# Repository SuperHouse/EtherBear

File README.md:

SuperHouse EtherBear
=====================

The EtherBear is an Arduino compatible development board for the
ATmega1284P microcontroller, with a Wiznet W6100 Ethernet interface and
Power-over-Ethernet support.

The W6100 provides both IPv4 and IPv6 support.

Features:

 * LEDs visible on the edge
 * USB-C Connector
 * I2C MAC address ROM
 * Overlay guide where you need it (both top and bottom)
 * D13 pin works for everything
 * RX pin biased
 * Mounting holes

More information is available at:

  https://www.superhouse.tv/etherbear

Hardware
--------
The "Hardware" directory contains the PCB design as an EAGLE project.
EAGLE PCB design software is available from Autodesk free for
non-commercial use.

Credits
-------
 * Jonathan Oxer <jon@oxer.com.au>

The EtherBear is based on the EtherUNO, which in turn is based on the
EtherTen, which was designed by Jonathan Oxer and Marc Alexander.

License
-------
Copyright 2020 SuperHouse Automation Pty Ltd  www.superhouse.tv  

The hardware portion of this project is licensed under the TAPR Open
Hardware License (www.tapr.org/OHL). The "license" folder within this
repository contains a copy of this license in plain text format.

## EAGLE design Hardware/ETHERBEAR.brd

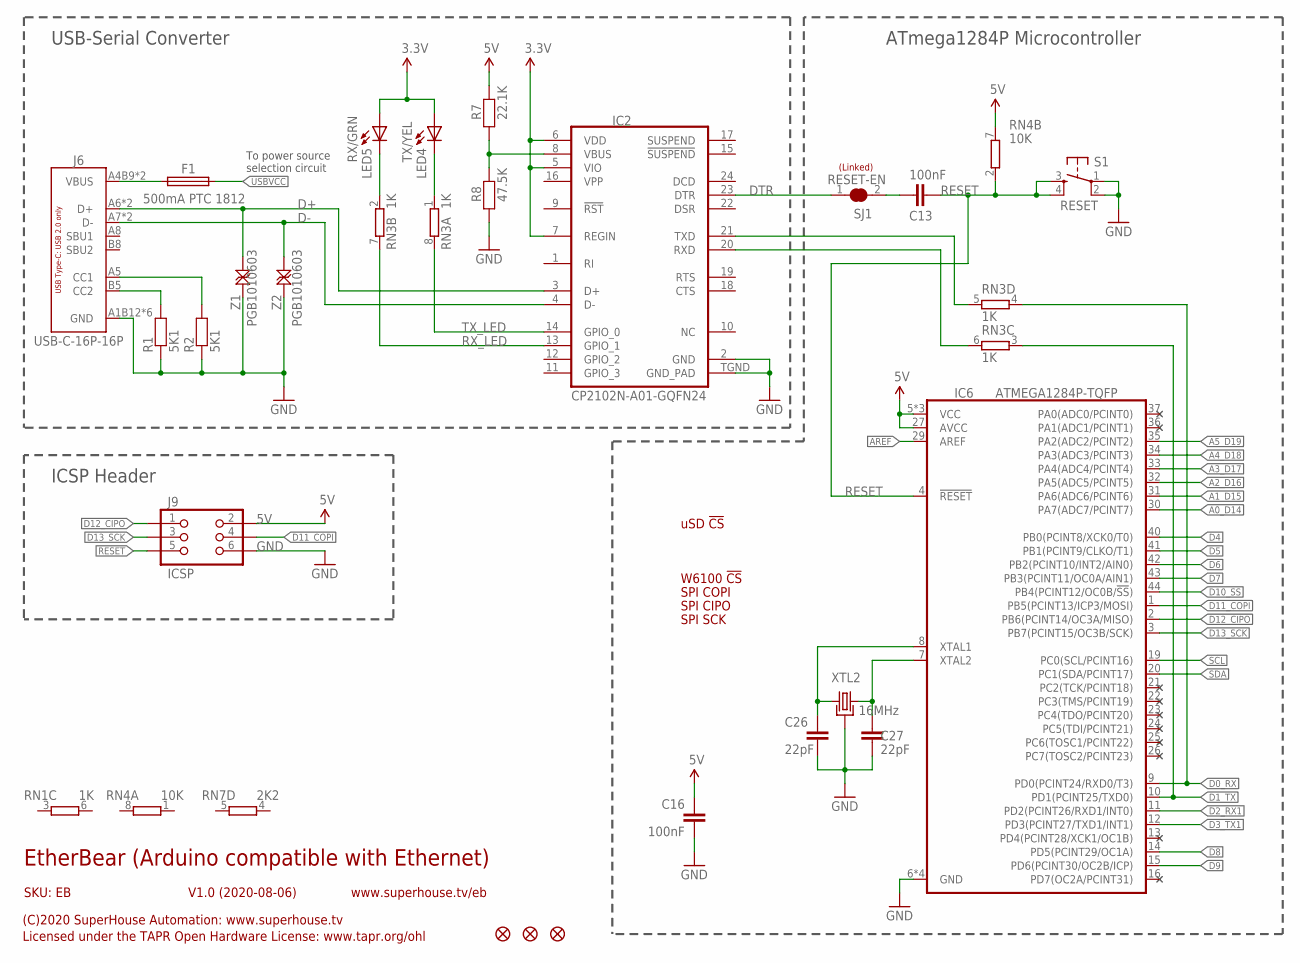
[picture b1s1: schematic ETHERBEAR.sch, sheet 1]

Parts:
C13, C16: 100nF; C0603
C26, C27: 22pF; C0603
F1: 500mA PTC 1812; 1812
FID1, FID2, FID3: FIDUCIAL1X2.5; FIDUCIAL-1X2.5
IC2: CP2102N-A01-GQFN24; QFN-24
IC6: ATMEGA1284P-TQFP; TQFP44
J6: USB-C-16P-16P; USB-C-16P
J9: ICSP; 2X03-ICSP
LED4: TX/YEL; LED-0603
LED5: RX/GRN; LED-0603
R1, R2: 5K1; R0603
R7: 22.1K; R0603
R8: 47.5K; R0603
RN1, RN3: 1K; CAY16
RN4: 10K; CAY16
RN7: 2K2; CAY16
S1: RESET; TACTILE_SMT-6MM
SJ1: RESET-EN; SJC
XTL2: 16MHz; CRYSTAL-SMD-3X2
Z1, Z2: PGB1010603; TVS0603

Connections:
3.3V: IC2.5 (VIO), IC2.6 (VDD), IC2.7 (REGIN), LED4.A, LED5.A; also elsewhere on the board
5V: C16.1, IC6.5 (VCC), IC6.17 (VCC), IC6.27 (AVCC), IC6.28 (VCC), J9.2, R7.2, RN4.7 (2); also elsewhere on the board
A0_D14: IC6.30 (PA7(ADC7/PCINT7)); also elsewhere on the board
A1_D15: IC6.31 (PA6(ADC6/PCINT6)); also elsewhere on the board
A2_D16: IC6.32 (PA5(ADC5/PCINT5)); also elsewhere on the board
A3_D17: IC6.33 (PA4(ADC4/PCINT4)); also elsewhere on the board
A4_D18: IC6.34 (PA3(ADC3/PCINT3)); also elsewhere on the board
A5_D19: IC6.35 (PA2(ADC2/PCINT2)); also elsewhere on the board
AREF: IC6.29 (AREF); also elsewhere on the board
D0_RX: IC6.9 (PD0(PCINT24/RXD0/T3)), RN3.4 (1); also elsewhere on the board
D1_TX: IC6.10 (PD1(PCINT25/TXD0)), RN3.3 (1); also elsewhere on the board
D2_RX1: IC6.11 (PD2(PCINT26/RXD1/INT0)); also elsewhere on the board
D3_TX1: IC6.12 (PD3(PCINT27/TXD1/INT1)); also elsewhere on the board
D4: IC6.40 (PB0(PCINT8/XCK0/T0)); also elsewhere on the board
D5: IC6.41 (PB1(PCINT9/CLKO/T1)); also elsewhere on the board
D6: IC6.42 (PB2(PCINT10/INT2/AIN0)); also elsewhere on the board
D7: IC6.43 (PB3(PCINT11/OC0A/AIN1)); also elsewhere on the board
D8: IC6.14 (PD5(PCINT29/OC1A)); also elsewhere on the board
D9: IC6.15 (PD6(PCINT30/OC2B/ICP)); also elsewhere on the board
D10_SS: IC6.44 (PB4(PCINT12/OC0B/!SS!))
D11_COPI: IC6.1 (PB5(PCINT13/ICP3/MOSI)), J9.4; also elsewhere on the board
D12_CIPO: IC6.2 (PB6(PCINT14/OC3A/MISO)), J9.1; also elsewhere on the board
D13_SCK: IC6.3 (PB7(PCINT15/OC3B/SCK)), J9.3; also elsewhere on the board
D+: IC2.3 (D+), J6.A6 (D+), J6.B6 (D+), Z1.1
D-: IC2.4 (D-), J6.A7 (D-), J6.B7 (D-), Z2.1
DTR: IC2.23 (DTR), SJ1.1
GND: C16.2, C26.1, C27.1, IC2.2 (GND), IC2.TGND (GND_PAD), IC6.6 (GND), IC6.18 (GND), IC6.38 (GND), IC6.39 (GND), J6.A1B12 (GND), J6.A12B1 (GND), J6.FIX1 (GND), J6.FIX2 (GND), J6.FIX3 (GND), J6.FIX4 (GND), J9.6, R1.1, R2.1, R8.1, S1.1, S1.2, XTL2.2 (GND), XTL2.4 (GND), Z1.2, Z2.2; also elsewhere on the board
unnamed: C26.2, IC6.8 (XTAL1), XTL2.1
unnamed: C13.1, SJ1.2
unnamed: C27.2, IC6.7 (XTAL2), XTL2.3 (2)
unnamed: J6.B5 (CC2), R1.2
unnamed: LED5.C, RN3.2 (1)
unnamed: LED4.C, RN3.1
unnamed: J6.A5 (CC1), R2.2
unnamed: IC2.8 (VBUS), R7.1, R8.2
unnamed: F1.1, J6.A4B9 (VBUS), J6.A9B4 (VBUS)
RESET: C13.2, IC6.4 (!RESET), J9.5, RN4.2 (1), S1.3, S1.4; also elsewhere on the board
RX_LED: IC2.13 (GPIO_1), RN3.7 (2)
SCL: IC6.19 (PC0(SCL/PCINT16)); also elsewhere on the board
SDA: IC6.20 (PC1(SDA/PCINT17)); also elsewhere on the board
TX_LED: IC2.14 (GPIO_0), RN3.8 (2)
USBRXD: IC2.21 (TXD), RN3.5 (2)
USBTXD: IC2.20 (RXD), RN3.6 (2)
USBVCC: F1.2; also elsewhere on the board

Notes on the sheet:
(Linked)
EtherBear (Arduino compatible with Ethernet)
SKU: EB
(C)2020 SuperHouse Automation: www.superhouse.tv
Licensed under the TAPR Open Hardware License: www.tapr.org/ohl
www.superhouse.tv/eb
V1.0 (2020-08-06)
USB-Serial Converter
ATmega1284P Microcontroller
ICSP Header
To power source selection circuit
uSD !CS
W6100 !CS
SPI COPI
SPI CIPO
SPI SCK

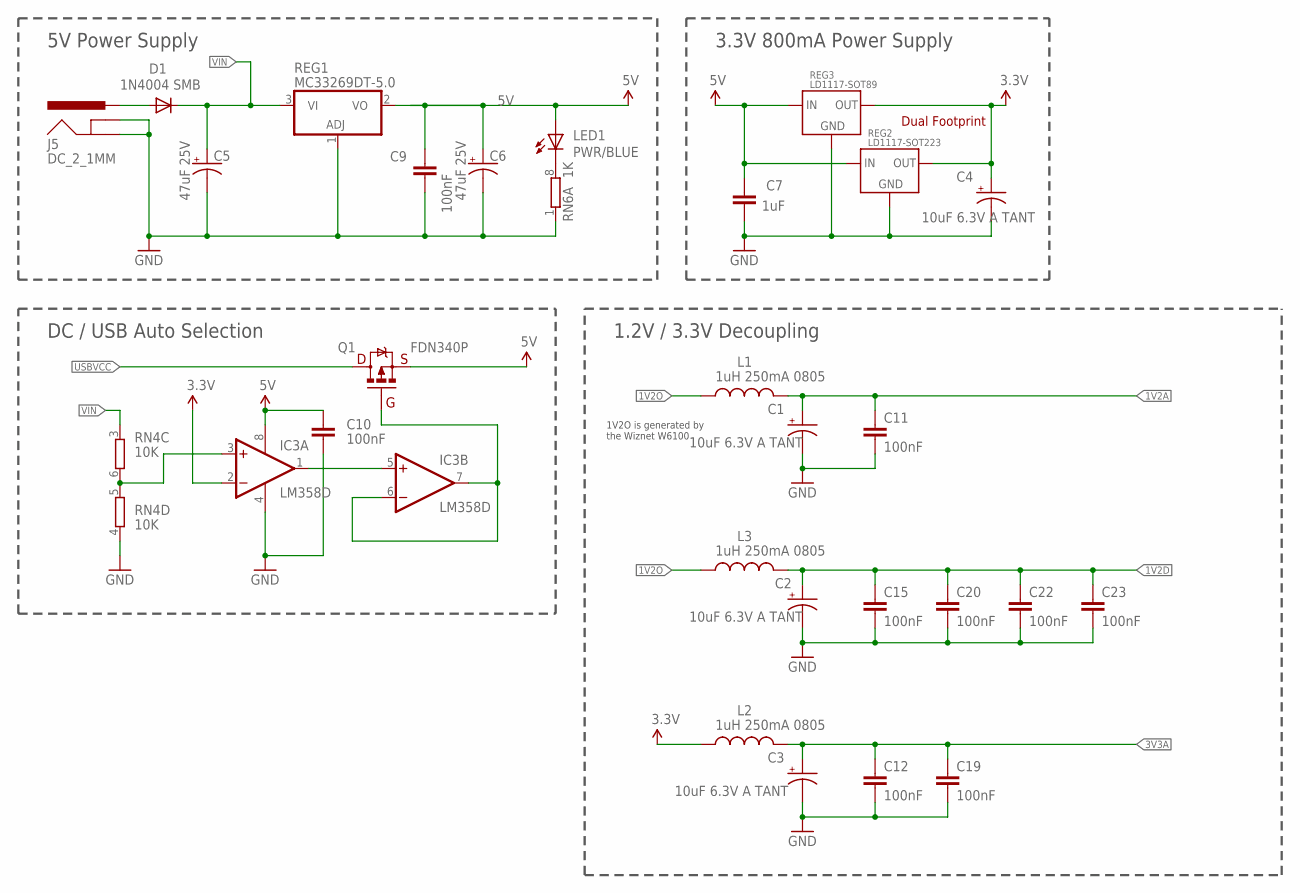
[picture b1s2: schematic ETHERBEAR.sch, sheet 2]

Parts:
C1, C2, C3, C4: 10uF 6.3V A TANT; EIA3216
C5, C6: 47uF 25V; PANASONIC_D
C7: 1uF; C0603
C9, C10, C11, C12, C15, C19, C20, C22, C23: 100nF; C0603
D1: 1N4004 SMB; SMA-DIODE
IC3: LM358D; SO08
J5: DC_2_1MM; POWER_JACK_SLOTS
L1, L2, L3: 1uH 250mA 0805; 0805-LARGE
LED1: PWR/BLUE; LED-0603
Q1: FDN340P; SOT23
REG1: MC33269DT-5.0; DPACK
REG2: LD1117-SOT223; SOT-223
REG3: LD1117-SOT89; SOT89
RN4: 10K; CAY16
RN6: 1K; CAY16

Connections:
1V2A: C1.A (+), C11.1, L1.2; also elsewhere on the board
1V2D: C2.A (+), C15.1, C20.1, C22.1, C23.1, L3.2; also elsewhere on the board
1V2O: L1.1, L3.1; also elsewhere on the board
3.3V: C4.A (+), IC3.2 (-IN), L2.1, REG2.2 (OUT), REG2.4 (OUT), REG3.2 (OUT), REG3.4 (OUT); also elsewhere on the board
3V3A: C3.A (+), C12.1, C19.1, L2.2; also elsewhere on the board
5V: C6.+, C7.1, C9.1, C10.1, IC3.8 (V+), LED1.A, Q1.2 (S), REG1.2 (VO), REG2.3 (IN), REG3.3 (IN); also elsewhere on the board
GND: C1.C (-), C2.C (-), C3.C (-), C4.C (-), C5.-, C6.-, C7.2, C9.2, C10.2, C11.2, C12.2, C15.2, C19.2, C20.2, C22.2, C23.2, IC3.4 (V-), J5.GND, J5.GNDBREAK, REG1.1 (ADJ), REG2.1 (GND), REG3.1 (GND), RN4.4 (1), RN6.1; also elsewhere on the board
unnamed: IC3.3 (+IN), RN4.5 (2), RN4.6 (2)
unnamed: LED1.C, RN6.8 (2)
unnamed: IC3.6 (-IN), IC3.7 (OUT), Q1.1 (G)
unnamed: IC3.1 (OUT), IC3.5 (+IN)
unnamed: D1.A, J5.PWR
USBVCC: Q1.3 (D); also elsewhere on the board
VIN: C5.+, D1.C, REG1.3 (VI), RN4.3 (1); also elsewhere on the board

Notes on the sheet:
Dual Footprint
1V2O is generated by the Wiznet W6100
1.2V / 3.3V Decoupling
3.3V 800mA Power Supply
5V Power Supply
DC / USB Auto Selection

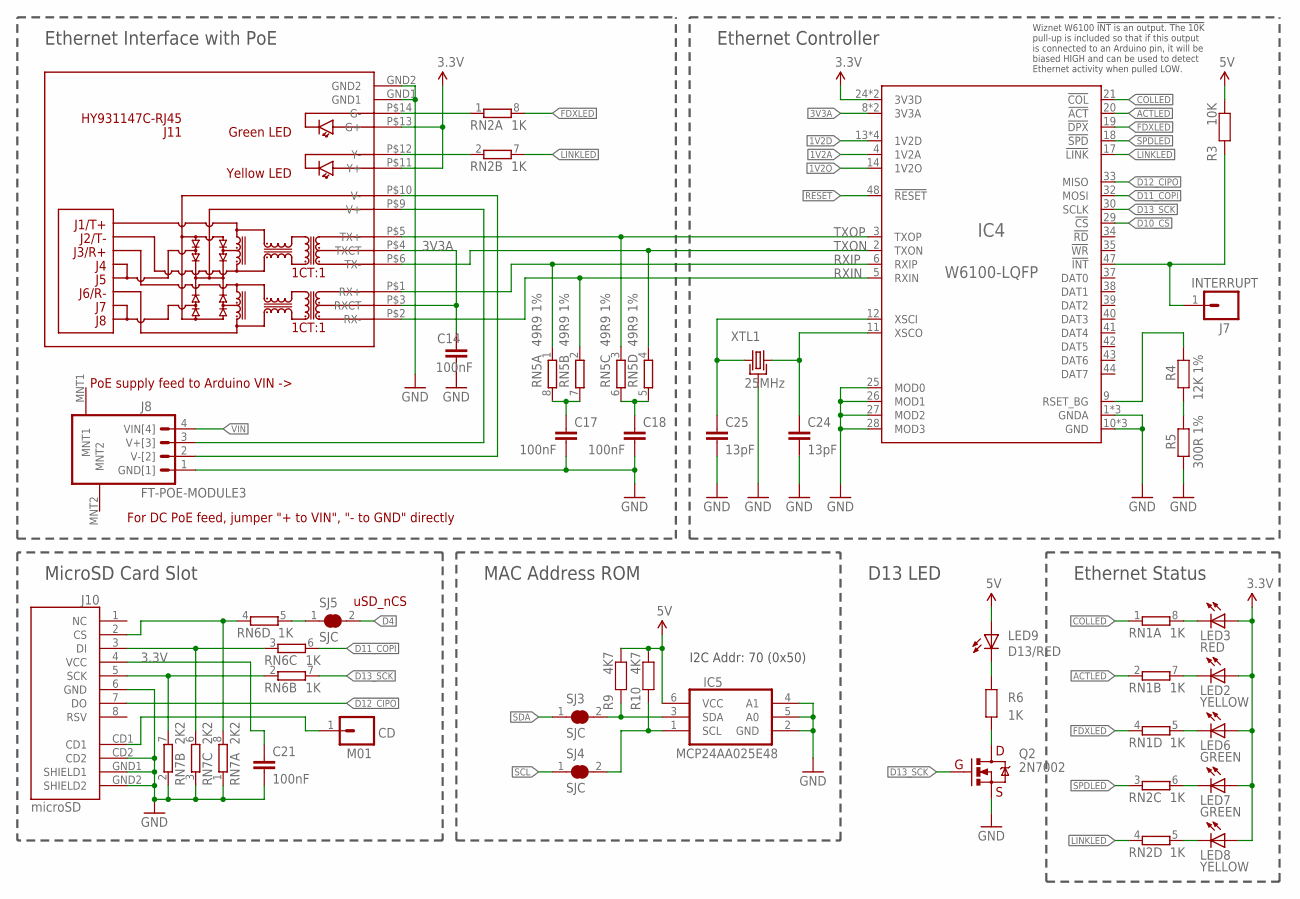
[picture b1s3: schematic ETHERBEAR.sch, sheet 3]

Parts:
C14, C17, C18, C21: 100nF; C0603
C24, C25: 13pF; C0603
CD: M01; 1X01
IC4: W6100-LQFP; LQFP48
IC5: MCP24AA025E48; SOT23-6
J7: INTERRUPT; 1X01
J8: FT-POE-MODULE3; FT-POE-MODULE-NOLABEL
J10: microSD; MICRO-SD-SOCKET-PP
J11: HY931147C-RJ45; HY931147C
LED2, LED8: YELLOW; LED-0603
LED3: RED; LED-0603
LED6, LED7: GREEN; LED-0603
LED9: D13/RED; LED-0603
Q2: 2N7002; SOT23-3
R3: 10K; R0603
R4: 12K 1%; R0603
R5: 300R 1%; R0603
R6: 1K; R0603
R9, R10: 4K7; R0603
RN1, RN2, RN6: 1K; CAY16
RN5: 49R9 1%; CAY16
RN7: 2K2; CAY16
SJ3, SJ4, SJ5: SJC
XTL1: 25MHz; CRYSTAL-SMD-3X2

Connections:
1V2A: IC4.4 (1V2A); also elsewhere on the board
1V2D: IC4.13 (1V2D), IC4.22 (1V2D), IC4.31 (1V2D), IC4.45 (1V2D); also elsewhere on the board
1V2O: IC4.14 (1V2O); also elsewhere on the board
3.3V: C21.1, IC4.24 (3V3D), IC4.36 (3V3D), J10.4 (VCC), J11.P$11 (Y+), J11.P$13 (G+), LED2.A, LED3.A, LED6.A, LED7.A, LED8.A; also elsewhere on the board
3V3A: C14.1, IC4.8 (3V3A), IC4.15 (3V3A), J11.P$3 (RXCT), J11.P$4 (TXCT); also elsewhere on the board
5V: IC5.6 (VCC), LED9.A, R3.1, R9.1, R10.1; also elsewhere on the board
ACTLED: IC4.20 (!ACT), RN1.2 (1)
COLLED: IC4.21 (!COL), RN1.1
D4: SJ5.2; also elsewhere on the board
D10_CS: IC4.29 (!CS); also elsewhere on the board
D11_COPI: IC4.32 (MOSI), RN6.6 (2); also elsewhere on the board
D12_CIPO: IC4.33 (MISO), J10.7 (DO); also elsewhere on the board
D13_SCK: IC4.30 (SCLK), Q2.1 (G), RN6.7 (2); also elsewhere on the board
FDXLED: IC4.19 (!DPX), RN1.4 (1), RN2.8 (2)
GND: C14.2, C17.2, C18.2, C21.2, C24.2, C25.2, IC4.1 (GNDA), IC4.7 (GNDA), IC4.10 (GND), IC4.16 (GNDA), IC4.23 (GND), IC4.25 (MOD0), IC4.26 (MOD1), IC4.27 (MOD2), IC4.28 (MOD3), IC4.46 (GND), IC5.2 (GND), IC5.4 (A1), IC5.5 (A0), J8.1 (GND[1]), J10.6 (GND), J10.CD2, J10.GND1 (SHIELD1), J10.GND2 (SHIELD2), J11.GND1, J11.GND2, Q2.2 (S), R5.2, RN7.1, RN7.2 (1), RN7.3 (1), XTL1.2 (GND), XTL1.4 (GND); also elsewhere on the board
LINKLED: IC4.17 (!LINK), RN2.4 (1), RN2.7 (2)
unnamed: C18.1, RN5.5 (2), RN5.6 (2)
unnamed: LED9.C, R6.2
unnamed: IC5.1 (SCL), R10.2, SJ4.2
unnamed: Q2.3 (D), R6.1
unnamed: LED3.C, RN1.8 (2)
unnamed: IC4.47 (!INT), J7.1, R3.2
unnamed: J10.2 (CS), RN6.4 (1), RN7.8 (2)
unnamed: CD.1, J10.CD1
unnamed: J10.5 (SCK), RN6.2 (1), RN7.7 (2)
unnamed: J10.3 (DI), RN6.3 (1), RN7.6 (2)
unnamed: LED7.C, RN2.6 (2)
unnamed: RN6.5 (2), SJ5.1
unnamed: LED8.C, RN2.5 (2)
unnamed: IC5.3 (SDA), R9.2, SJ3.2
unnamed: C24.1, IC4.11 (XSCO), XTL1.3 (2)
unnamed: C25.1, IC4.12 (XSCI), XTL1.1
unnamed: R4.2, R5.1
unnamed: IC4.9 (RSET_BG), R4.1
unnamed: J11.P$14 (G-), RN2.1
unnamed: J8.3 (V+[3]), J11.P$9 (V+)
unnamed: J8.2 (V-[2]), J11.P$10 (V-)
unnamed: C17.1, RN5.7 (2), RN5.8 (2)
unnamed: LED6.C, RN1.5 (2)
unnamed: LED2.C, RN1.7 (2)
unnamed: J11.P$12 (Y-), RN2.2 (1)
RESET: IC4.48 (!RESET); also elsewhere on the board
RXIN: IC4.5 (RXIN), J11.P$2 (RX-), RN5.2 (1)
RXIP: IC4.6 (RXIP), J11.P$1 (RX+), RN5.1
SCL: SJ4.1; also elsewhere on the board
SDA: SJ3.1; also elsewhere on the board
SPDLED: IC4.18 (!SPD), RN2.3 (1)
TXON: IC4.2 (TXON), J11.P$6 (TX-), RN5.4 (1)
TXOP: IC4.3 (TXOP), J11.P$5 (TX+), RN5.3 (1)
VIN: J8.4 (VIN[4]); also elsewhere on the board

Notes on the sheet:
PoE supply feed to Arduino VIN ->
For DC PoE feed, jumper "+ to VIN", "- to GND" directly
I2C Addr: 70 (0x50)
uSD_nCS
Ethernet Interface with PoE
Ethernet Controller
MAC Address ROM
MicroSD Card Slot
Ethernet Status
Wiznet W6100 !INT is an output. The 10K pull-up is included so that if this output is connected to an Arduino pin, it will be biased HIGH and can be used to detect Ethernet activity when pulled LOW.
D13 LED

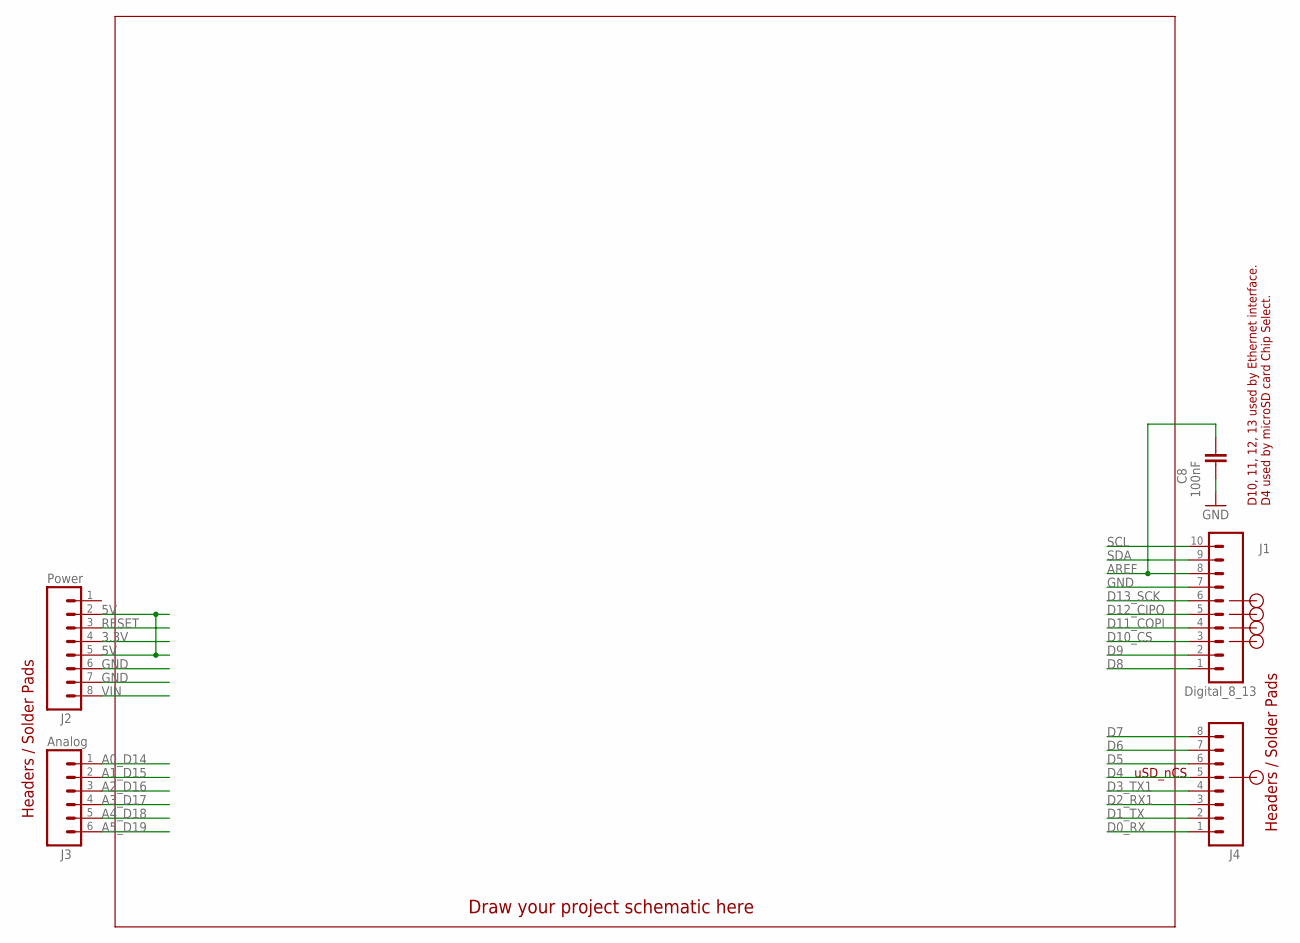
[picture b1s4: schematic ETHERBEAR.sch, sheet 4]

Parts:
C8: 100nF; C0603
J1: Digital_8_13; 1X10-S
J2: Power; 1X08-S
J3: Analog; 1X06-S
J4: Digital_0_7; 1X08-S

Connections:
3.3V: J2.4; also elsewhere on the board
5V: J2.2, J2.5; also elsewhere on the board
A0_D14: J3.1; also elsewhere on the board
A1_D15: J3.2; also elsewhere on the board
A2_D16: J3.3; also elsewhere on the board
A3_D17: J3.4; also elsewhere on the board
A4_D18: J3.5; also elsewhere on the board
A5_D19: J3.6; also elsewhere on the board
AREF: C8.1, J1.8; also elsewhere on the board
D0_RX: J4.1; also elsewhere on the board
D1_TX: J4.2; also elsewhere on the board
D2_RX1: J4.3; also elsewhere on the board
D3_TX1: J4.4; also elsewhere on the board
D4: J4.5; also elsewhere on the board
D5: J4.6; also elsewhere on the board
D6: J4.7; also elsewhere on the board
D7: J4.8; also elsewhere on the board
D8: J1.1; also elsewhere on the board
D9: J1.2; also elsewhere on the board
D10_CS: J1.3; also elsewhere on the board
D11_COPI: J1.4; also elsewhere on the board
D12_CIPO: J1.5; also elsewhere on the board
D13_SCK: J1.6; also elsewhere on the board
GND: C8.2, J1.7, J2.6, J2.7; also elsewhere on the board
RESET: J2.3; also elsewhere on the board
SCL: J1.10; also elsewhere on the board
SDA: J1.9; also elsewhere on the board
VIN: J2.8; also elsewhere on the board

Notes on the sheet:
Headers / Solder Pads
Draw your project schematic here
D10, 11, 12, 13 used by Ethernet interface.
uSD_nCS
D4 used by microSD card Chip Select.

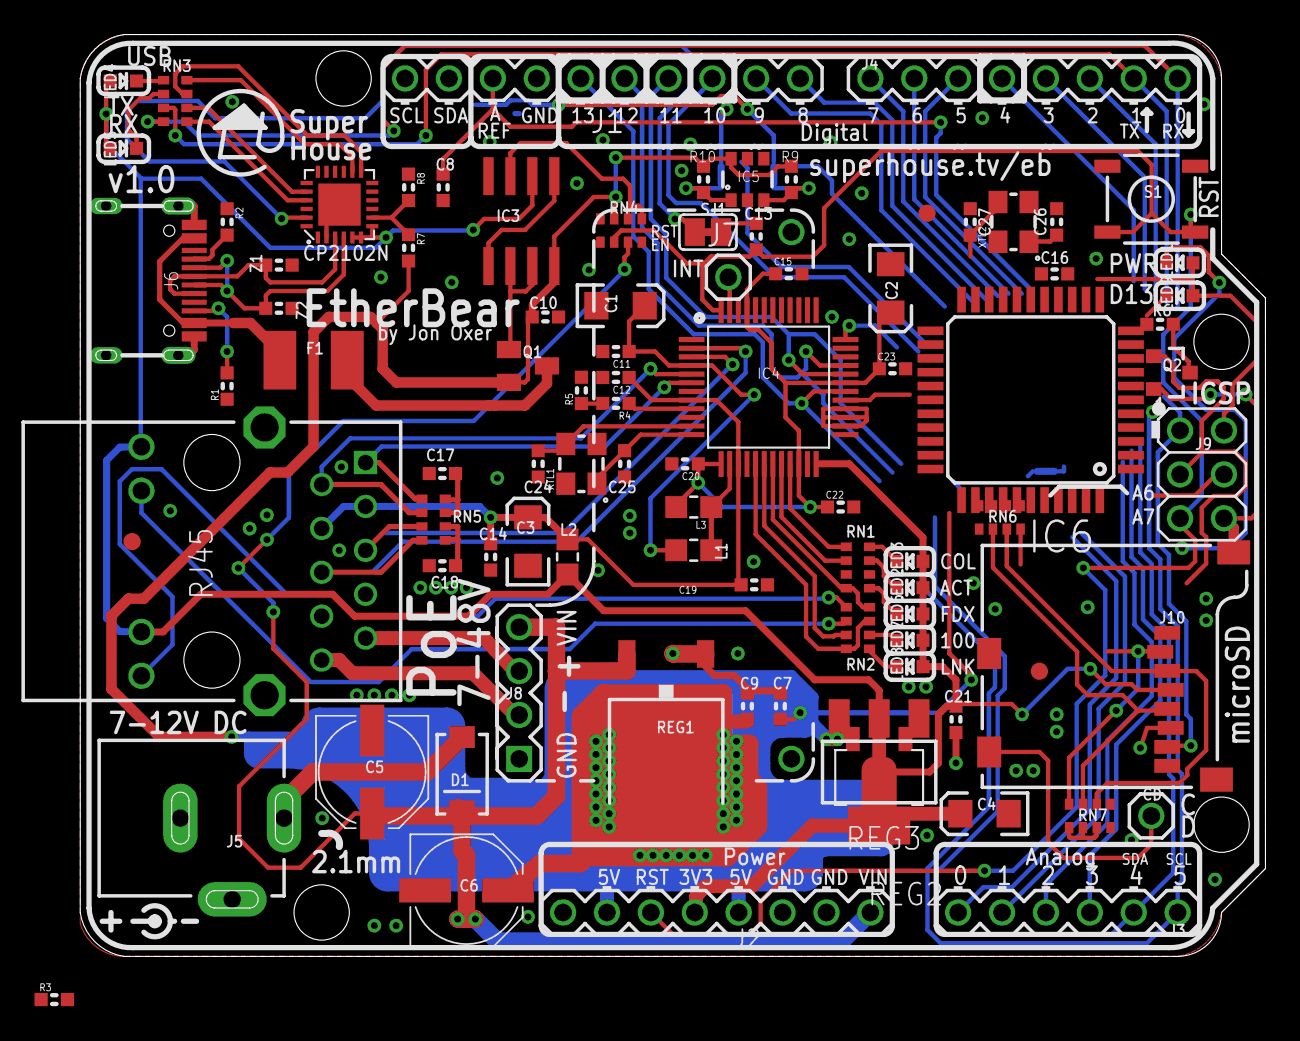
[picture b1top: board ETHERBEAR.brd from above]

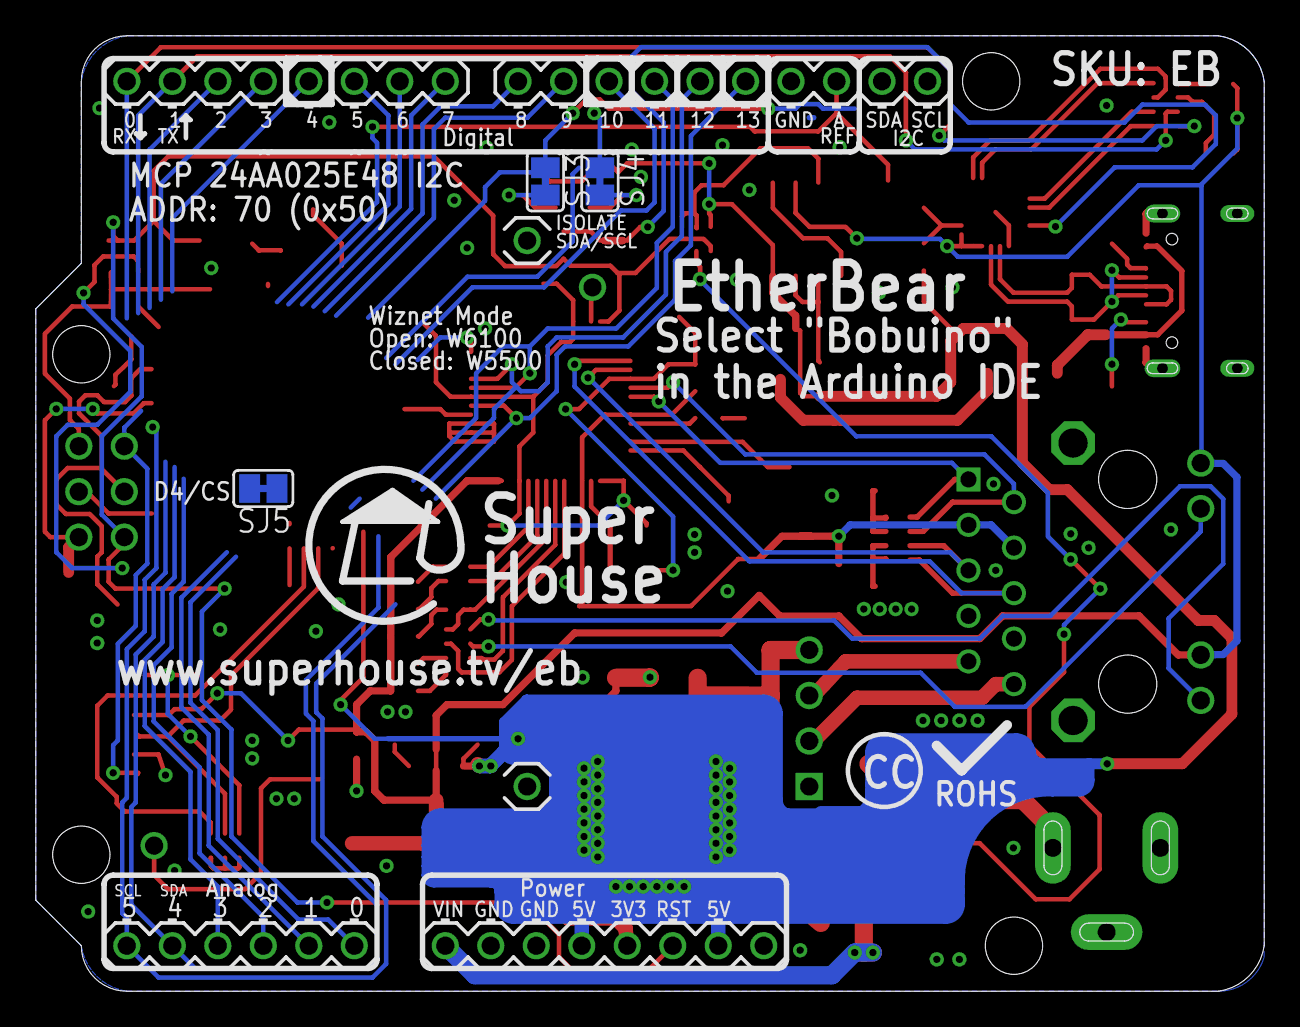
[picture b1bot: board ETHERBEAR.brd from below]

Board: 2 copper layers, 68.6 x 53.3 mm, 92 parts (3 on the bottom side), 88 nets.

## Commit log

2020-08-10 Credits
2020-08-10 Added schematics for other W6100 boards
2020-08-10 Schematic changes for ATmega1284P
2020-08-10 Fixed README after forking from EtherUNO
2020-08-10 Fixed project name
